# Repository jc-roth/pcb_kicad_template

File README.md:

# pcb_kicad_template
KiCAD template for Hammond 1475/Eurocard format

## Installing
Download the repo and drag it into your KiCAD template folder (this is set by the `KICAD_USER_TEMPLATE_DIR` environment variable). When selecting `File > New Project from Template` this template should appear as an option.

## Features

- 100mm eurocard format, fits inside [Hammond 1457 series enclosures](https://www.hammfg.com/electronics/small-case/extruded/1457-emi).Alternatively place inside a [Schroff 24563131 Eurocard subrack](https://www.digikey.com/en/products/detail/schroff/24563131/4209922) or similar.
- [S10B-ZR-3.4 10-pin JST ZH connector](https://www.digikey.com/en/products/detail/jst-sales-america-inc/S10B-ZR-3-4/9972252) for power connections. Use with the [JST A10ZR10ZR28H51A cable](https://www.digikey.com/en/products/detail/jst-sales-america-inc/A10ZR10ZR28H51A/6708528).
- [S4B-PH-K-S 4-pin connector](https://www.digikey.com/en/products/detail/jst-sales-america-inc/S4B-PH-K-S/926628) for I2C connections. This is compatible with the [Adafruit STEMMA standard](https://learn.adafruit.com/introducing-adafruit-stemma-qt/what-is-stemma). Use with a cable from Adafruit, such as the [ST PH 2mm 4-Pin to Male Header Cable - I2C STEMMA Cable](https://www.digikey.com/en/products/detail/adafruit-industries-llc/3955/9745250) or [STEMMA Cable - 4 Pin JST-PH 2mm Cable-Female/Female](https://www.digikey.com/en/products/detail/adafruit-industries-llc/3568/7672337).
- x6 [Amphenol 132289 SMA connectors](https://www.digikey.com/en/products/detail/amphenol-rf/132289/1989875), remove if unnecessary.

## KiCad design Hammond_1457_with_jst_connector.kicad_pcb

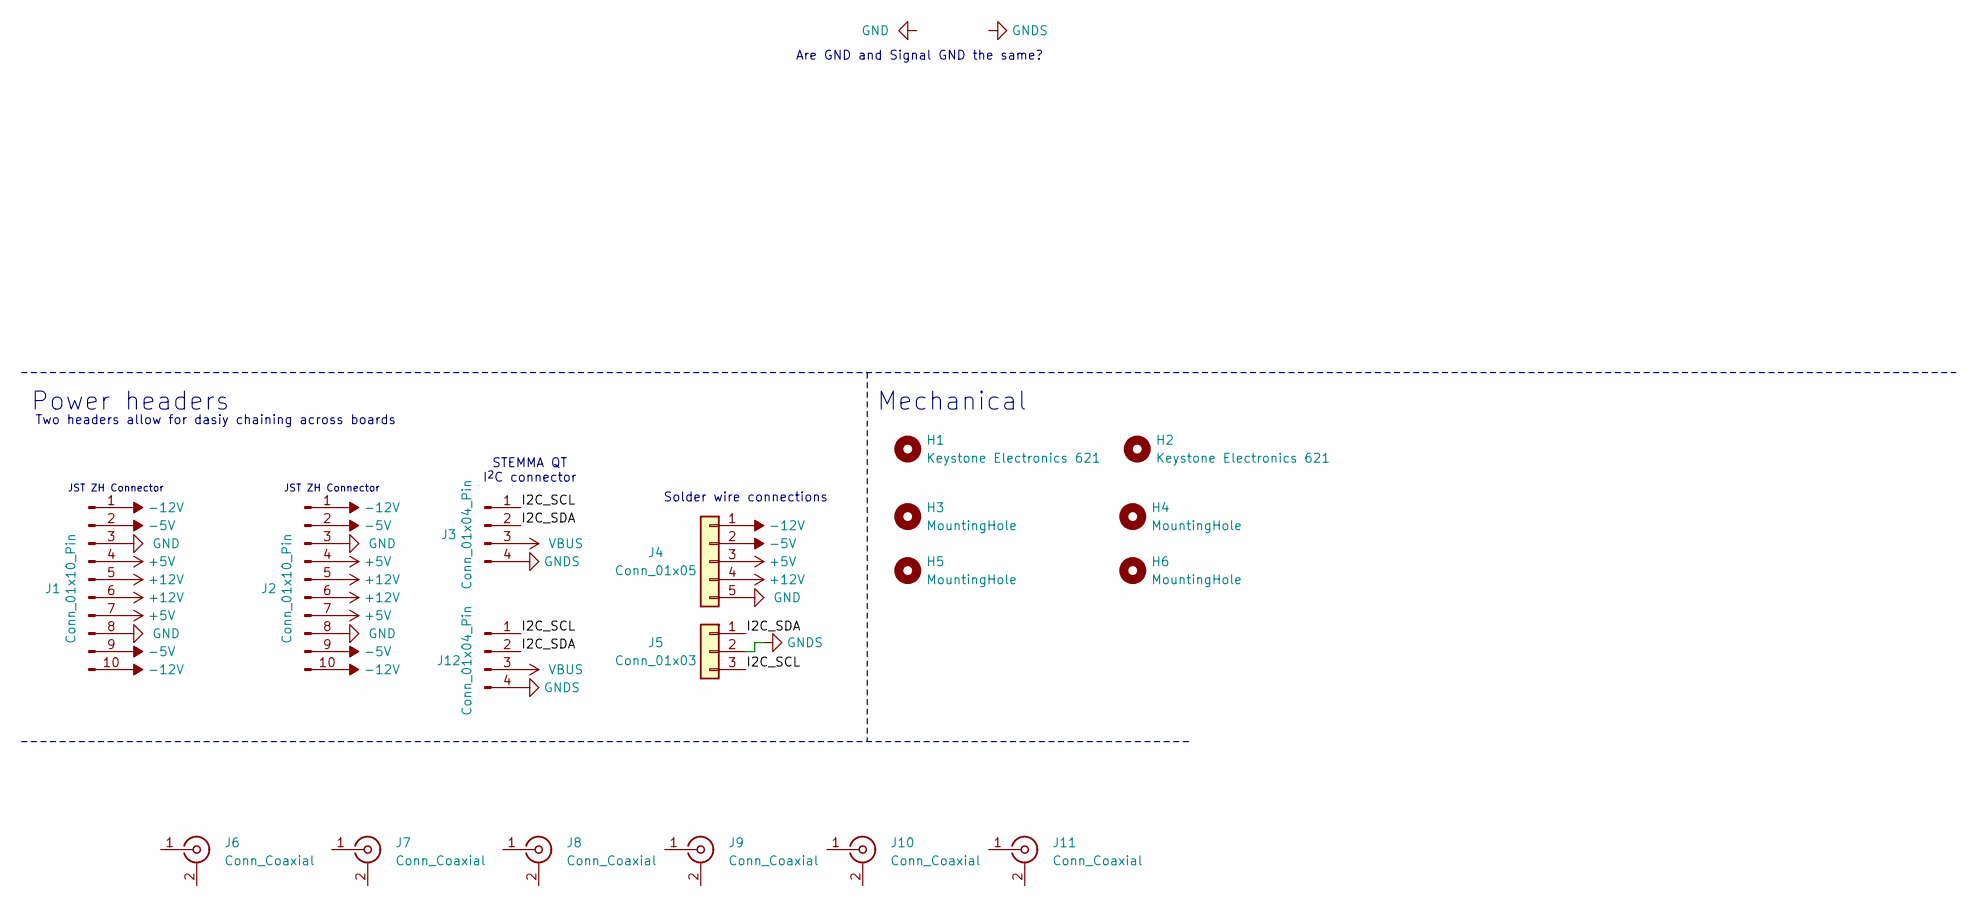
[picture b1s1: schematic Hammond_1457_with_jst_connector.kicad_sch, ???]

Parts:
H1, H2: Keystone Electronics 621; Keystone 621; Digikey PN 36-621-ND
H3, H4, H5, H6: MountingHole; MountingHole_3.2mm_M3
J1, J2: Conn_01x10_Pin; JST_ZH_B10B-ZR_1x10_P1.50mm_Vertical; Digikey PN 455-S10B-ZR-ND
J3, J12: Conn_01x04_Pin; JST_SH_SM04B-SRSS-TB_1x04-1MP_P1.00mm_Horizontal; Digikey PN 455-SM04B-SRSS-TBTR-ND
J4: Conn_01x05; SolderWire-0.75sqmm_1x05_P4.8mm_D1.25mm_OD2.3mm
J5: Conn_01x03; SolderWire-0.75sqmm_1x03_P4.8mm_D1.25mm_OD2.3mm
J6, J7, J8, J9, J10, J11: Conn_Coaxial; SMA_Amphenol_132289_EdgeMount; Digikey PN ACX1426-ND

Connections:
+5V: J1.4, J1.7, J2.4, J2.7, J4.3
+12V: J1.5, J1.6, J2.5, J2.6, J4.4
-5V: J1.2, J1.9, J2.2, J2.9, J4.2
-12V: J1.1, J1.10, J2.1, J2.10, J4.1
/I2C_SCL: J3.1, J5.3, J12.1
/I2C_SDA: J3.2, J5.1, J12.2
GND: J1.3, J1.8, J2.3, J2.8, J4.5
GNDS: J3.4, J5.2, J12.4
VBUS: J3.3, J12.3

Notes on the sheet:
Solder wire connections
Are GND and Signal GND the same?
Mechanical
STEMMA QT I^{2}C connector
JST ZH Connector
Power headers
Two headers allow for dasiy chaining across boards

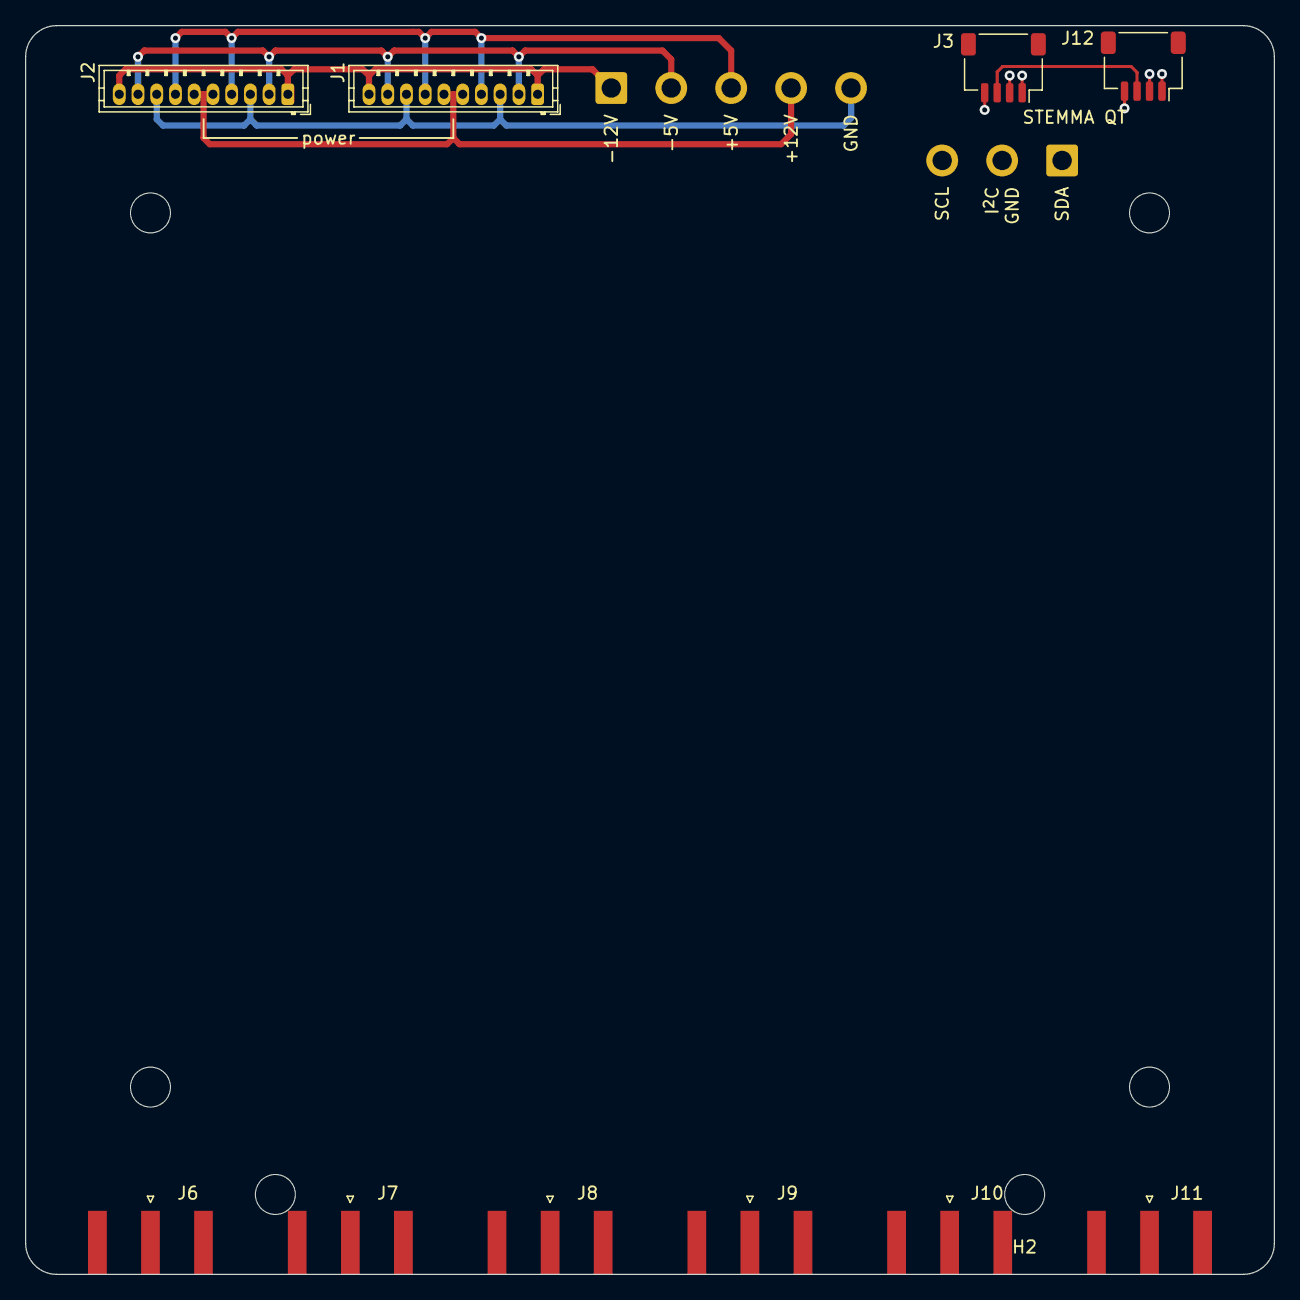
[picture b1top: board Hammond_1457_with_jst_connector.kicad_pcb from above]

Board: 4 copper layers, 100.0 x 100.0 mm, 18 parts (0 on the bottom side), 9 nets.

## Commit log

2025-09-29 Updated .gitignore and readme
2025-09-29 Added board and template meta file
2025-09-29 Moved board image
